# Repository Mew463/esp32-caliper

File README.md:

# Summary
This project adds bluetooth functionality to an ordinary set of calipers with an embedded ESP32 C3. It's main purpose was to speed up CAD Development with it's ability to automatically enter numbers into OnShape.

It features a built in 150mAh battery and a USB C interface for charging/uploading code. 

This is meant to be a direct replacement for the GROSS solution that you could just buy for the inexpensive price of $100:

# Features
- Realtime battery reporting
- Two User buttons 
    - Button1 enters numbers and then presses Enter
    - Button2 enters numbers and then inserts a space so that the user can add tolerance
- Neopixel indicator (States: Bluetooth pairing, Connected, Button 1 or 2 Pressed, Entering deep sleep)
- 20 day standby time or 2hr usage time 
- Charge light
- Snap-on PCB Case

# Decoding the Caliper Data
[Calipers Used](https://www.amazon.com/Neiko-01407A-Electronic-Digital-Stainless/dp/B000GSLKIW/ref=sr_1_1_sspa?crid=24I6FXWO3H5A4&keywords=neiko+caliper&qid=1678232283&sprefix=neiko+calip%2Caps%2C243&sr=8-1-spons&psc=1&spLa=ZW5jcnlwdGVkUXVhbGlmaWVyPUExQ0FaOFdNMVQ3TTImZW5jcnlwdGVkSWQ9QTA2ODI2NTAyUTFQWVNNVFVCQkZNJmVuY3J5cHRlZEFkSWQ9QTAyNTI0MDAzRERQVjZMWVAxWTExJndpZGdldE5hbWU9c3BfYXRmJmFjdGlvbj1jbGlja1JlZGlyZWN0JmRvTm90TG9nQ2xpY2s9dHJ1ZQ==)

## Soldering Wires
My old caliper's data output port looked like this:

Unfortunately I broke the old caliper during this project and had to buy a brand new version of my old caliper. Sometime in the span of 3 years, it seemed that the data output port changed to be adapted for a female micro usb (though there wasn't one soldered on the caliper's pcb).

The smaller pads made it more painful to solder wires to, but it was doable.

With an oscilloscope, I probed each pad to determine which was the clock, data, and ground line.

## Logic converter
Because the Caliper's logic level is 1.5v but the ESP32 is 3v3, I needed to use a logic converter. V1 and V3 use the transistor circuit below which shifts and inverts the clock and data lines coming from the caliper. V2 used a IC level shifter which didn't work at all for some unknown reason. 

 Logic converter

## Data protocol
Like many other people who have decoded their caliper, I discovered that there are 24 bits sent out by the caliper:

The bit at index[0] is always 1.

Bits from index[1] - index[15] signify the value with the LCB being first.

Index[21] signifies a negative number.

My old caliper had one bit to indicate the unit, but my new caliper did not have this bit (? idk why).

# Creation
## KiCAD
Designed in KiCAD 6.0. Bought from Mouser and manufactured by JLCPCB. I assembled them by hand.

## CAD

[CAD](https://cad.onshape.com/documents/368abd500c875635f19a3005/w/ab7db60efad03bd7d6054350/e/1cf117eaa5e9ddddb41ff0d8?renderMode=0&uiState=6407caa931dacb56d467d292)

# Summary 
This project took like 40 hours and 3 revisions of pcbs.
If you really want a bluetooth caliper just buy one premade, it'll save you a lot of headache. Otherwise this is a fun intro-to-embedded project.

[Premade bluetooth calipers](https://www.amazon.com/iGaging-Electronic-Absolute-Bluetooth-Connectivity/dp/B0716B8Q99/ref=sr_1_3?crid=NPXC9LKMF29V&keywords=bluetooth+caliper&qid=1678232538&s=hi&sprefix=bluetooth+calip%2Ctools%2C187&sr=1-3)

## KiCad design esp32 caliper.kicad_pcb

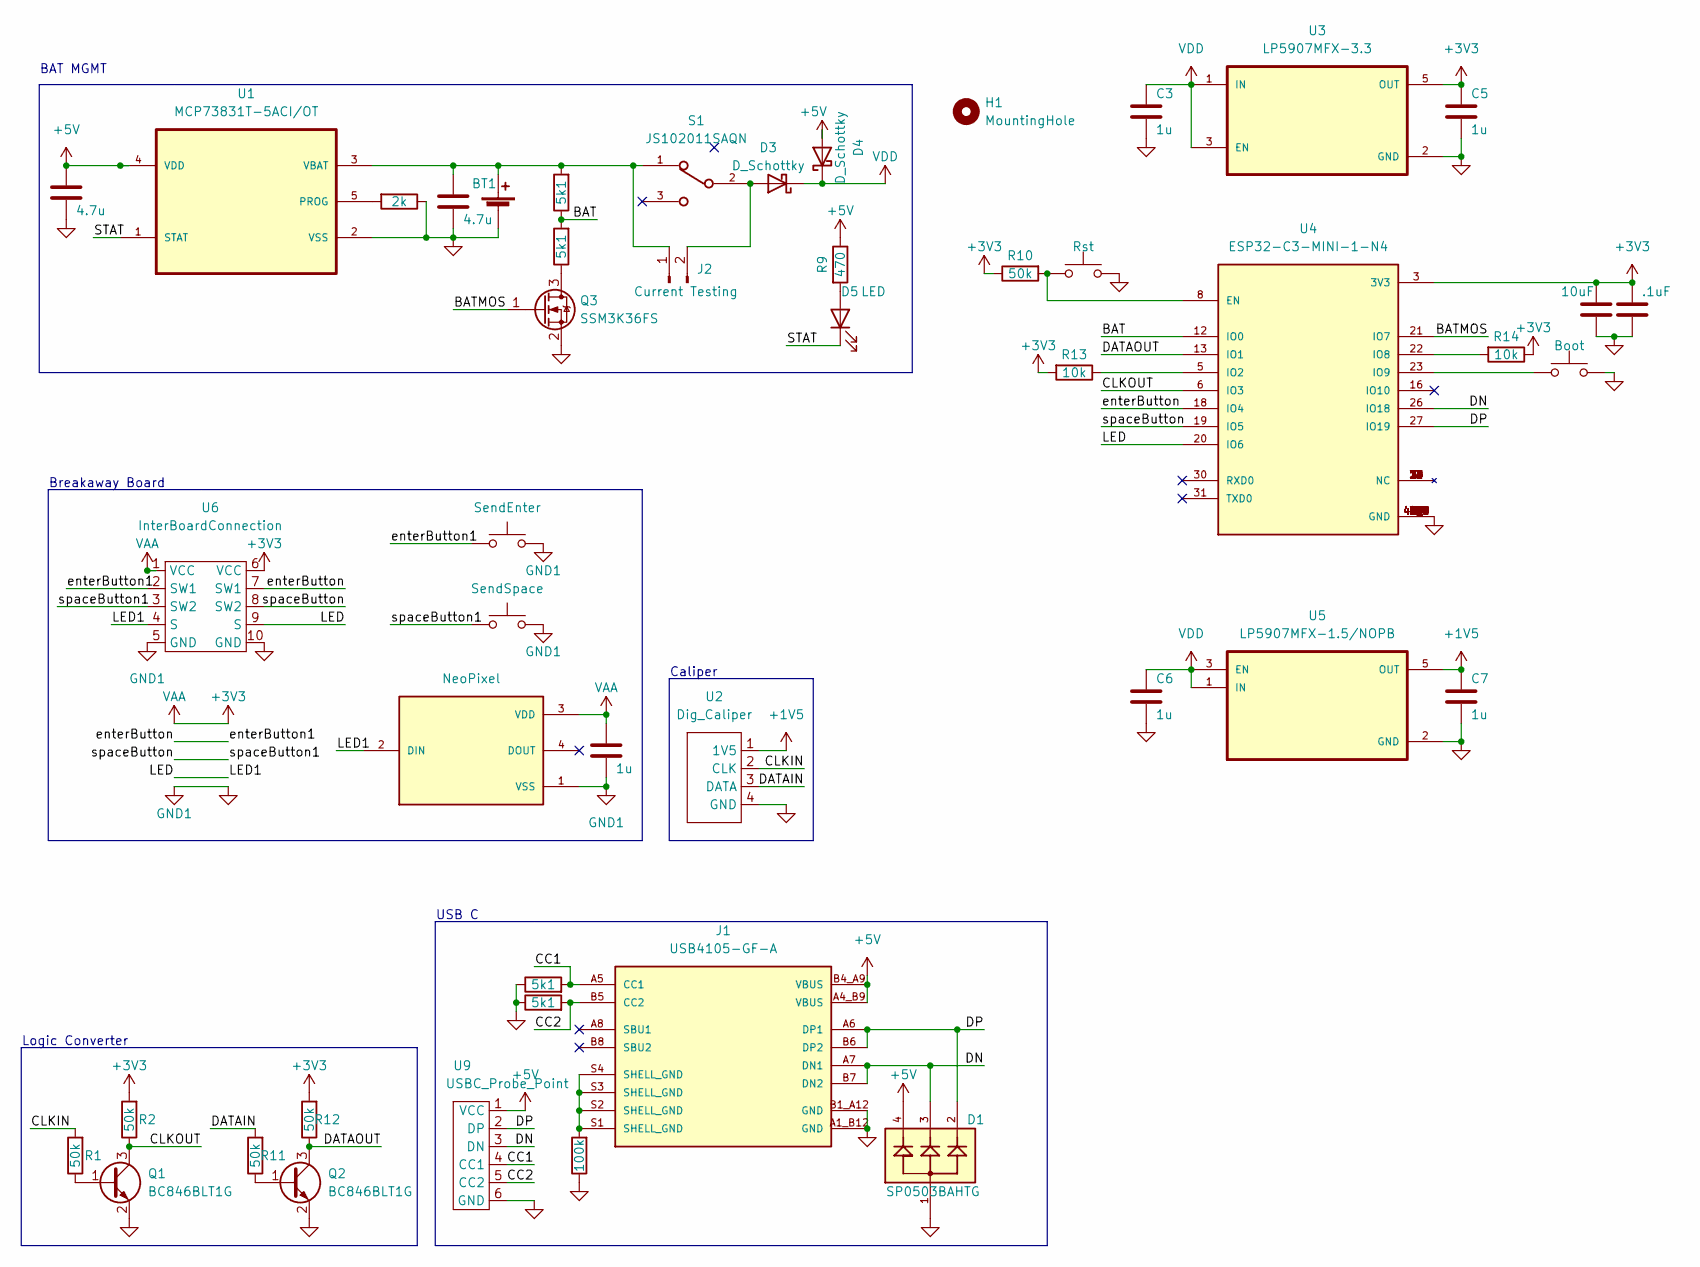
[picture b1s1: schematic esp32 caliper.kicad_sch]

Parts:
BT1: 3.7; Battery
C1, C2: 4.7u; C_0402_1005Metric
C3, C4, C5, C6, C7: 1u; C_0402_1005Metric
C9: 10uF; C_0402_1005Metric
C10: .1uF; C_0402_1005Metric
D1: SP0503BAHTG; SOT143; PARTREV N/A
D2: NeoPixel; LED_1655; PARTREV 01
D3, D4: D_Schottky; D_SOD-523
D5: LED; LED_0603_1608Metric
H1: MountingHole; MountingHole_3.2mm_M3
J1: USB4105-GF-A; GCT_USB4105-GF-A; PARTREV A3
J2: Current Testing; PinHeader_1x02_P1.00mm_Vertical
Q1, Q2: BC846BLT1G; SOT-23
Q3: SSM3K36FS; SOT-416
R1, R2, R10, R11, R12: 50k; R_0402_1005Metric
R3, R4, R5, R7: 5k1; R_0402_1005Metric
R6: 100k; R_0402_1005Metric
R8: 2k; R_0402_1005Metric
R9: 470; R_0402_1005Metric
R13, R14: 10k; R_0402_1005Metric
S1: JS102011SAQN; SW_JS102011SAQN
SW1: Boot; SW_Push_1P1T_NO_Vertical_Wuerth_434133025816
SW2: Rst; SW_Push_1P1T_NO_Vertical_Wuerth_434133025816
SW3: SendEnter; SW_Push_1P1T_NO_Vertical_Wuerth_434133025816
SW4: SendSpace; SW_Push_1P1T_NO_Vertical_Wuerth_434133025816
U1: MCP73831T-5ACI/OT; SOT95P280X145-5N; MPN MCP73831T-5ACI/OT
U2: Dig_Caliper; Caliper
U3: LP5907MFX-3.3; SOT95P280X145-5N
U4: ESP32-C3-MINI-1-N4; XCVR_ESP32-C3-MINI-1-N4; PARTREV v1.0
U5: LP5907MFX-1.5/NOPB; SOT95P280X145-5N
U6: InterBoardConnection
U9: USBC_Probe_Point; PinHeader_1x06_P1.00mm_Vertical

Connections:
+1V5: C7.1, U2.1 (1V5), U5.5 (OUT)
+3V3: C4.1, C5.1, C9.1, C10.1, D2.3 (VDD), R2.2, R10.1, R12.2, R13.2, R14.1, U3.5 (OUT), U4.3 (3V3), U6.1 (VCC), U6.6 (VCC)
+5V: C1.1, D1.4, D4.2 (A), J1.A4_B9 (VBUS), J1.B4_A9 (VBUS), R9.1, U1.4 (VDD), U9.1 (VCC)
/BAT: R3.1, R7.2, U4.12 (IO0)
/BATMOS: Q3.1 (G), U4.21 (IO7)
/CC1: J1.A5 (CC1), R4.2, U9.4 (CC1)
/CC2: J1.B5 (CC2), R5.2, U9.5 (CC2)
/CLKIN: R1.2, U2.2 (CLK)
/CLKOUT: Q1.3 (C), R2.1, U4.6 (IO3)
/DATAIN: R11.2, U2.3 (DATA)
/DATAOUT: Q2.3 (C), R12.1, U4.13 (IO1)
/DN: D1.3, J1.A7 (DN1), J1.B7 (DN2), U4.26 (IO18), U9.3 (DN)
/DP: D1.2, J1.A6 (DP1), J1.B6 (DP2), U4.27 (IO19), U9.2 (DP)
/LED: D2.2 (DIN), U4.20 (IO6), U6.4 (S), U6.9 (S)
/STAT: D5.1 (K), U1.1 (STAT)
/enterButton: SW3.1, U4.18 (IO4), U6.2 (SW1), U6.7 (SW1)
/spaceButton: SW4.1, U4.19 (IO5), U6.3 (SW2), U6.8 (SW2)
GND: BT1.2 (-), C1.2, C2.2, C3.2, C4.2, C5.2, C6.2, C7.2, C9.2, C10.2, D1.1, D2.1 (VSS), J1.A1_B12 (GND), J1.B1_A12 (GND), Q1.2 (E), Q2.2 (E), Q3.2 (S), R4.1, R5.1, R6.1, R8.1, SW1.2, SW2.1, SW3.2, SW4.2, U1.2 (VSS), U2.4 (GND), U3.2 (GND), U4.1 (GND), U4.2 (GND), U4.11 (GND), U4.14 (GND), U4.36 (GND), U4.37 (GND), U4.38 (GND), U4.39 (GND), U4.40 (GND), U4.41 (GND), U4.42 (GND), U4.43 (GND), U4.44 (GND), U4.45 (GND), U4.46 (GND), U4.47 (GND), U4.48 (GND), U4.49_1 (GND), U4.49_2 (GND), U4.49_3 (GND), U4.49_4 (GND), U4.49_5 (GND), U4.49_6 (GND), U4.49_7 (GND), U4.49_8 (GND), U4.49_9 (GND), U4.50 (GND), U4.51 (GND), U4.52 (GND), U4.53 (GND), U5.2 (GND), U6.5 (GND), U6.10 (GND), U9.6 (GND)
unnamed: BT1.1 (+), C2.1, J2.1, R3.2, S1.1, U1.3 (VBAT)
unnamed: D3.2 (A), J2.2, S1.2
unnamed: D5.2 (A), R9.2
unnamed: J1.S1 (SHELL_GND), J1.S2 (SHELL_GND), J1.S3 (SHELL_GND), J1.S4 (SHELL_GND), R6.2
unnamed: Q1.1 (B), R1.1
unnamed: Q2.1 (B), R11.1
unnamed: Q3.3 (D), R7.1
unnamed: R8.2, U1.5 (PROG)
unnamed: R10.2, SW2.2, U4.8 (EN)
unnamed: R13.1, U4.5 (IO2)
unnamed: R14.2, U4.22 (IO8)
unnamed: SW1.1, U4.23 (IO9)
VDD: C3.1, C6.1, D3.1 (K), D4.1 (K), U3.1 (IN), U3.3 (EN), U5.1 (IN), U5.3 (EN)

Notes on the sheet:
Breakaway Board
USB C
Logic Converter
Caliper
BAT MGMT

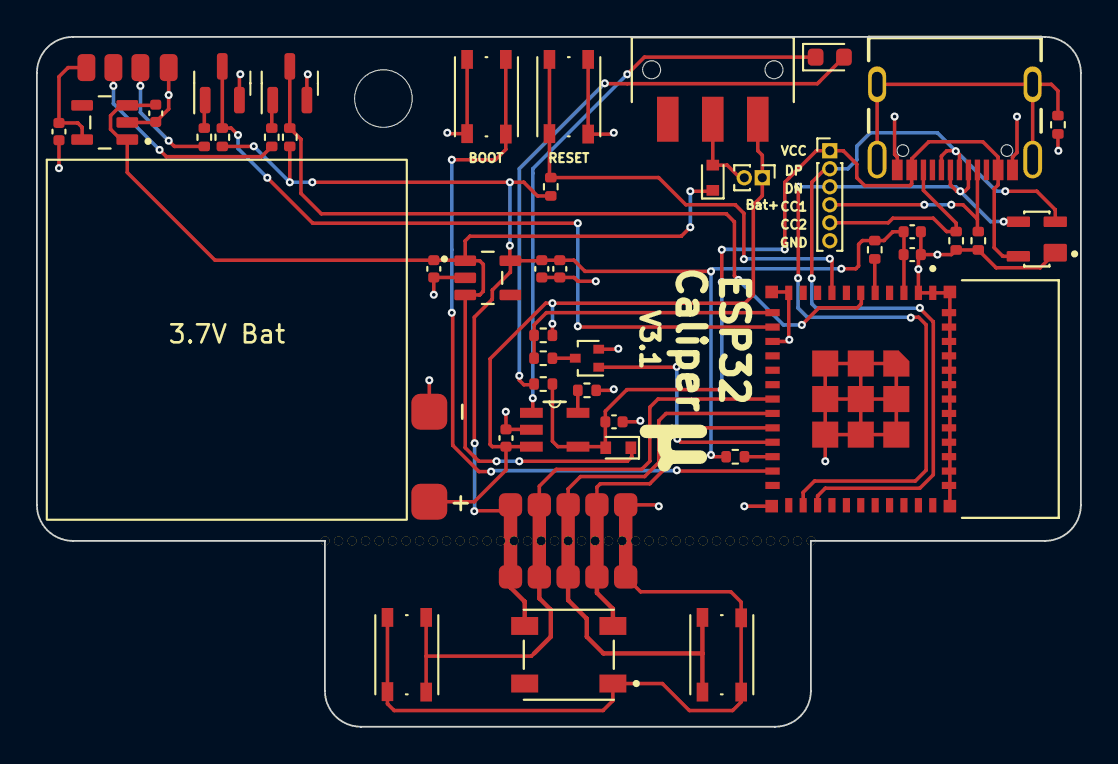
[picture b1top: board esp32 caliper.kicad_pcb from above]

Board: 2 copper layers, 58.0 x 38.3 mm, 47 parts (0 on the bottom side), 31 nets.

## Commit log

2023-03-07 test image
2023-03-07 uploaded images
2023-03-08 more gifs
2023-03-08 some editing
2023-03-08 more imagess
2023-03-08 updated images
2023-03-08 almost done
2023-03-08 fixed random spelling error and uploaded arduino code
2023-03-10 updated some images
2023-03-10 update file links
2023-03-13 add .gitignore
2023-03-13 add 1.5v output
2023-03-13 Drop files from .gitignore
